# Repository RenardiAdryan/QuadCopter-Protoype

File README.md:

# QuadCopter-Protoype

This project is a basic drone flight controller using PID controller

if you have inquiries
Please feel free to contact me!

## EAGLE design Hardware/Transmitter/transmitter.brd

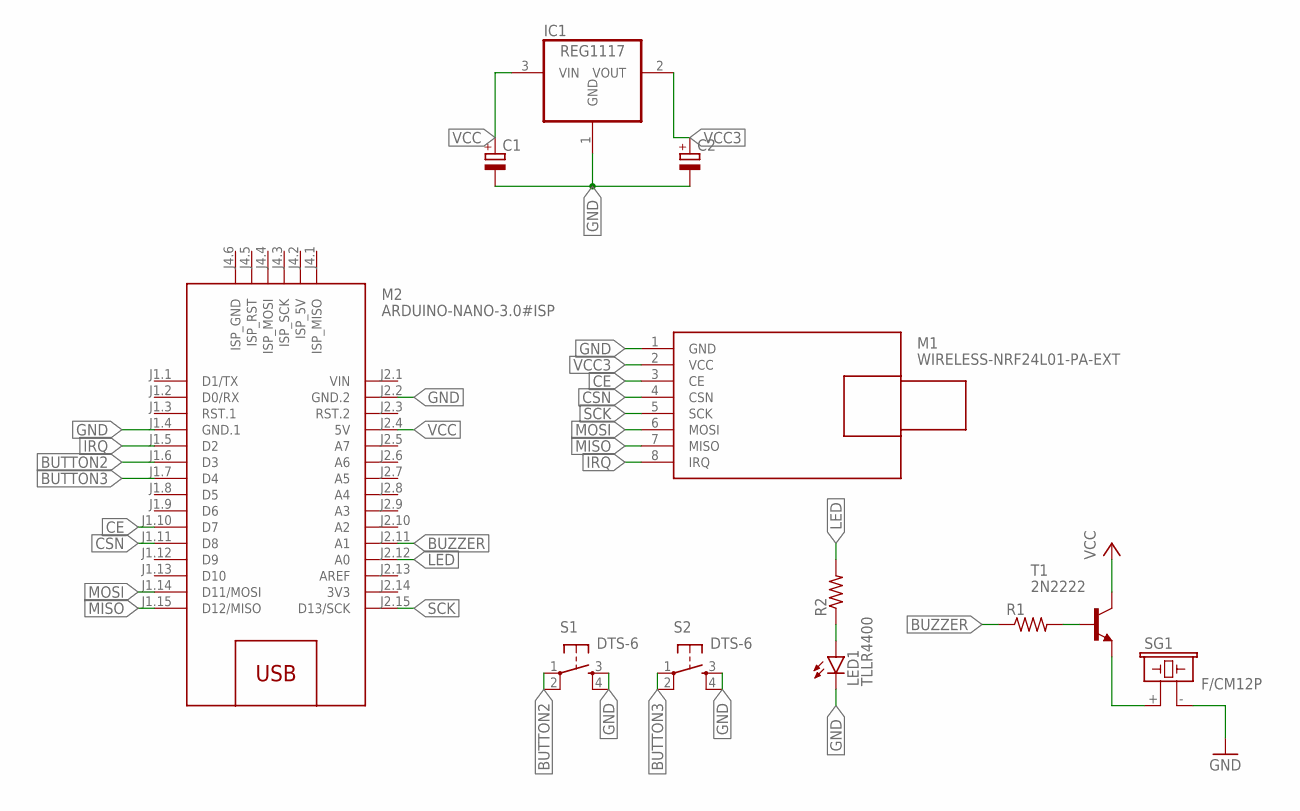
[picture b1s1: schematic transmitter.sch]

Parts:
C1, C2: CPOL-EUE2,5-6E; E2,5-6E
IC1: REG1117; SOT223
LED1: TLLR4400; LED3MM
M1: WIRELESS-NRF24L01-PA-EXT
M2: ARDUINO-NANO-3.0#ISP
R1, R2: R-US_R0805; R0805
S1, S2: DTS-6
SG1: F/CM12P
T1: 2N2222; TO92-EBC-OVAL

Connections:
3V3: M2.J2.14 (3V3)
BUTTON2: M2.J1.6 (D3), S1.1, S1.2
BUTTON3: M2.J1.7 (D4), S2.1, S2.2
BUZZER: M2.J2.11 (A1), R1.1
CE: M1.3 (CE), M2.J1.10 (D7)
CSN: M1.4 (CSN), M2.J1.11 (D8)
GND: C1.-, C2.-, IC1.1 (GND), LED1.K (C), M1.1 (GND), M2.J1.4 (GND.1), M2.J2.2 (GND.2), S1.3, S1.4, S2.3, S2.4, SG1.- (2)
IRQ: M1.8 (IRQ), M2.J1.5 (D2)
LED: M2.J2.12 (A0), R2.2
MISO: M1.7 (MISO), M2.J1.15 (D12/MISO)
MOSI: M1.6 (MOSI), M2.J1.14 (D11/MOSI)
unnamed: SG1.+ (1), T1.E
unnamed: R1.2, T1.B
unnamed: LED1.A, R2.1
SCK: M1.5 (SCK), M2.J2.15 (D13/SCK)
VCC: C1.+, IC1.3 (VIN), M2.J2.4 (5V), T1.C
VCC3: C2.+, IC1.2 (VOUT), M1.2 (VCC)
VIN: M2.J2.1 (VIN)

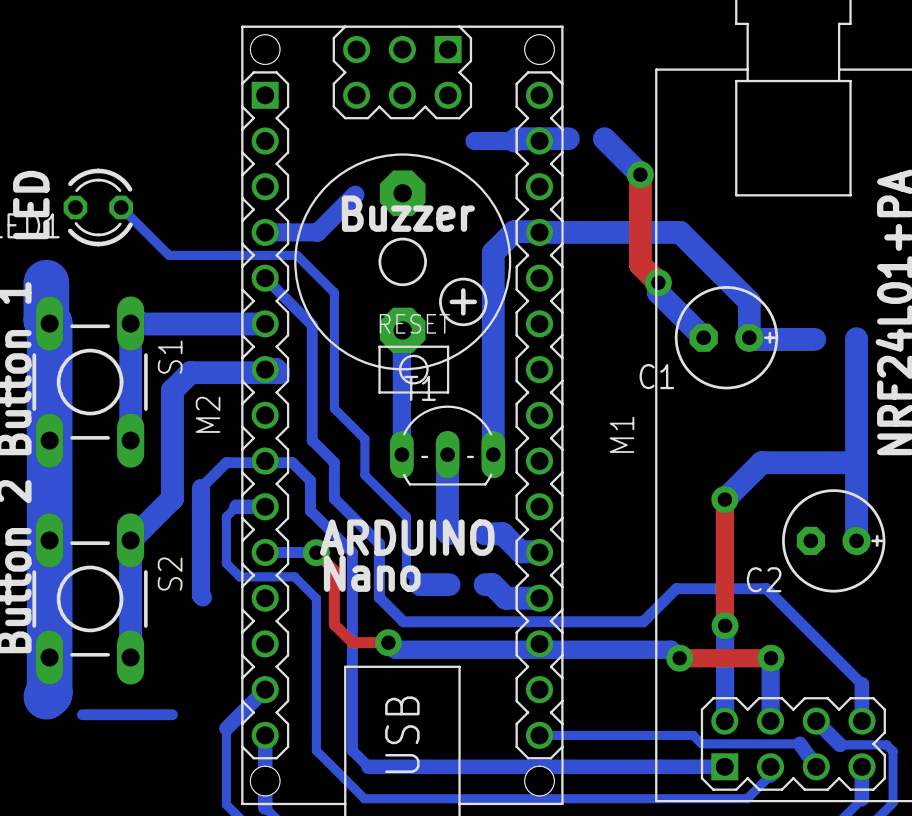
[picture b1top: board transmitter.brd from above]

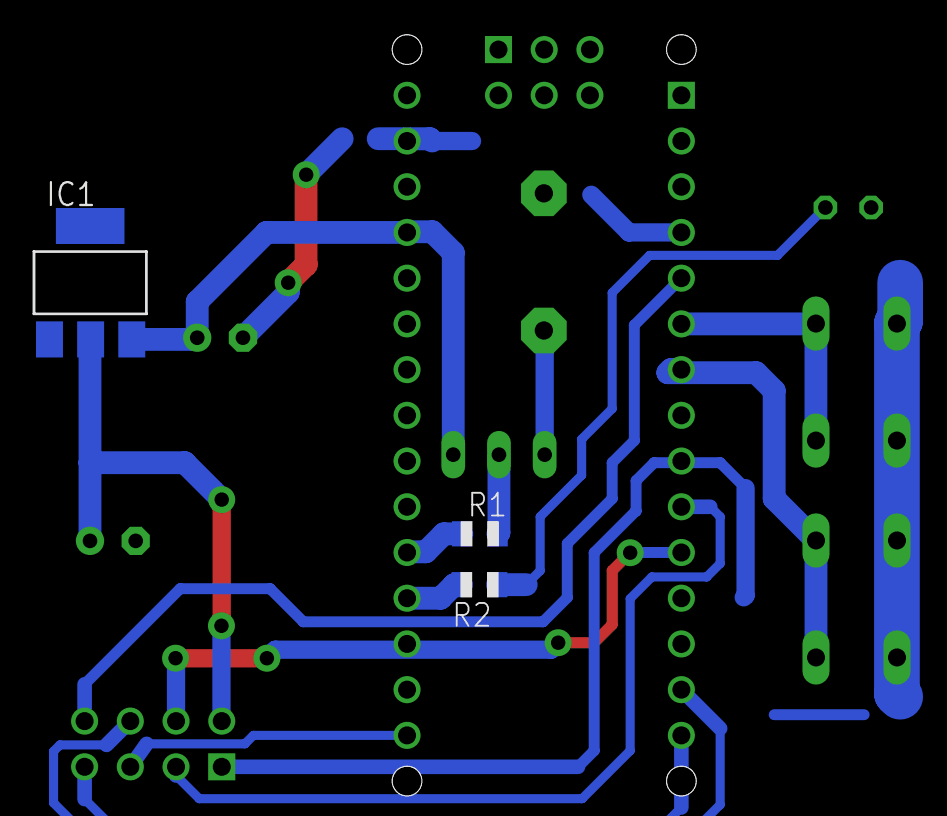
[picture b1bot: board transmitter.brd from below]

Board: 2 copper layers, 12 parts (3 on the bottom side), 16 nets.

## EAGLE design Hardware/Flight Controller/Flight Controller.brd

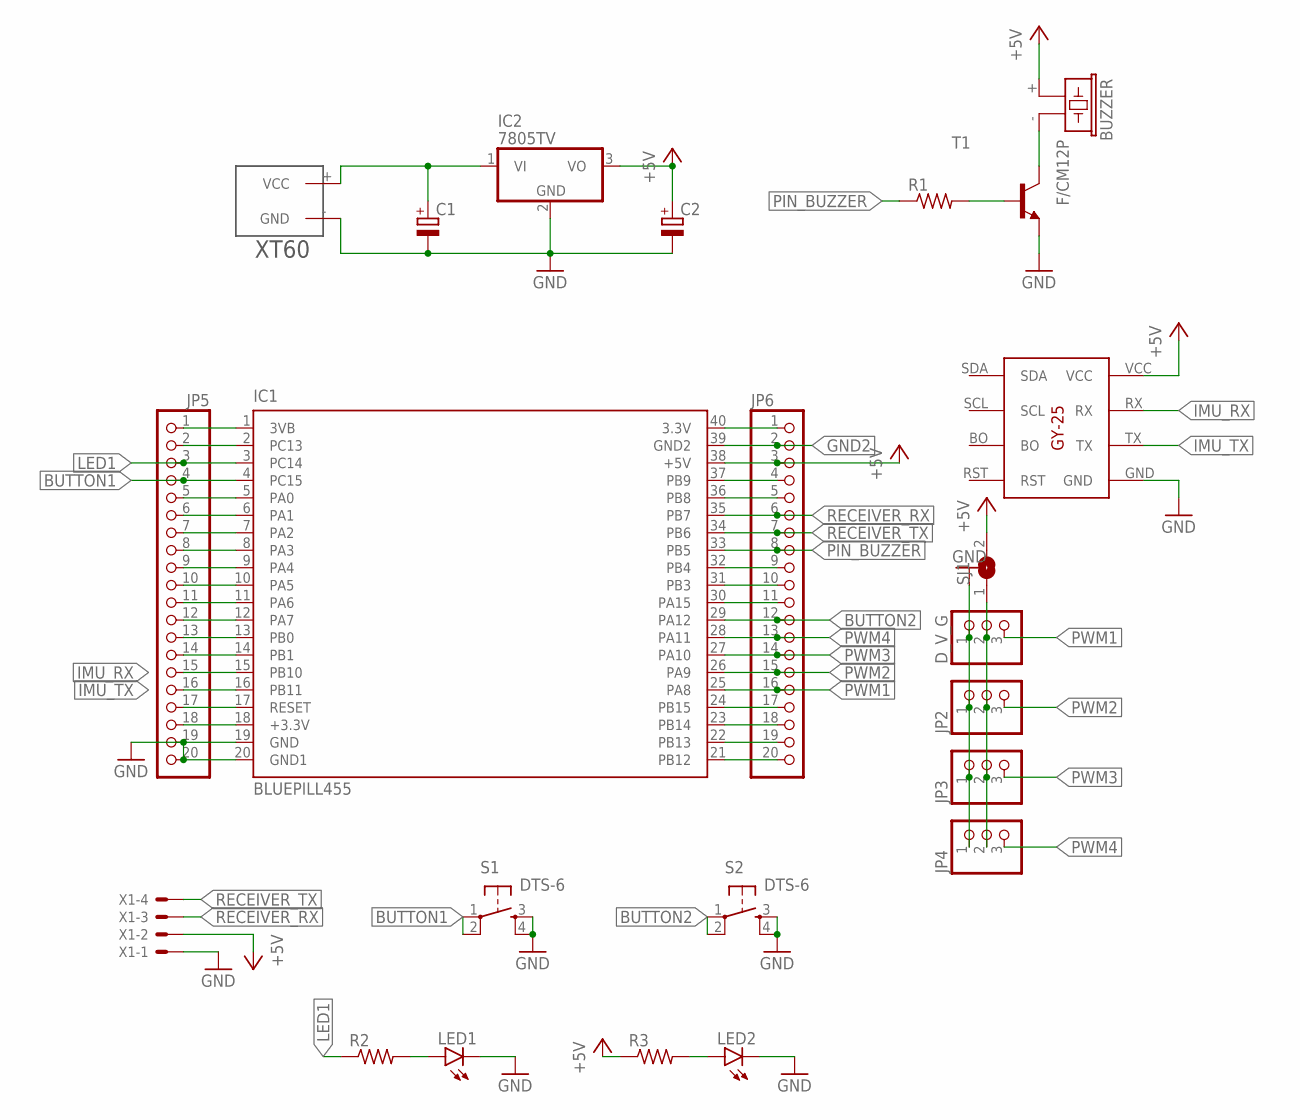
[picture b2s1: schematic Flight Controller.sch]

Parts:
BUZZER: F/CM12P
C1, C2: CPOL-EUE2,5-6E; E2,5-6E
D_V_G: PINHD-1X3; 1X03
GY-1: GY-25GY-25_INV; GY-25_INV
IC1: BLUEPILL455; DIL40
IC2: 7805TV; TO220V
JP2, JP3, JP4: PINHD-1X3; 1X03
JP5, JP6: PINHD-1X20; 1X20
LED1, LED2: LED3MM
R1, R2, R3: R-US_M0805; M0805
S1, S2: DTS-6
SJ1: SJ
T1: -NPN-TO92-EBC; TO92-EBC
U$1: XT60
X1: KK-156-4

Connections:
+5V: BUZZER.+ (1), C2.+, GY-1.VCC, IC1.38 (+5V), IC2.3 (VO), JP6.3, R3.1, SJ1.2, X1.2
BUTTON1: IC1.4 (PC15), JP5.4, S1.1, S1.2
BUTTON2: IC1.29 (PA12), JP6.12, S2.1, S2.2
GND: C1.-, C2.-, D_V_G.1, GY-1.GND, IC1.19 (GND), IC1.20 (GND1), IC2.2 (GND), JP2.1, JP3.1, JP4.1, JP5.19, JP5.20, LED1.K (C), LED2.K (C), S1.3, S1.4, S2.3, S2.4, T1.E, U$1.- (GND), X1.1
GND2: IC1.39 (GND2), JP6.2
IMU_RX: GY-1.RX, IC1.15 (PB10), JP5.15
IMU_TX: GY-1.TX, IC1.16 (PB11), JP5.16
LED1: IC1.3 (PC14), JP5.3, R2.1
unnamed: C1.+, IC2.1 (VI), U$1.+ (VCC)
unnamed: BUZZER.- (2), T1.C
unnamed: IC1.18 (+3.3V), JP5.18
unnamed: R1.2, T1.B
unnamed: IC1.17 (RESET), JP5.17
unnamed: IC1.14 (PB1), JP5.14
unnamed: IC1.13 (PB0), JP5.13
unnamed: IC1.12 (PA7), JP5.12
unnamed: IC1.11 (PA6), JP5.11
unnamed: IC1.10 (PA5), JP5.10
unnamed: IC1.9 (PA4), JP5.9
unnamed: IC1.8 (PA3), JP5.8
unnamed: IC1.7 (PA2), JP5.7
unnamed: IC1.6 (PA1), JP5.6
unnamed: IC1.5 (PA0), JP5.5
unnamed: LED1.A, R2.2
unnamed: LED2.A, R3.2
unnamed: IC1.2 (PC13), JP5.2
unnamed: IC1.1 (3VB), JP5.1
unnamed: IC1.40 (3.3V), JP6.1
unnamed: IC1.37 (PB9), JP6.4
unnamed: IC1.36 (PB8), JP6.5
unnamed: D_V_G.2, JP2.2, JP3.2, JP4.2, SJ1.1
unnamed: IC1.32 (PB4), JP6.9
unnamed: IC1.31 (PB3), JP6.10
unnamed: IC1.30 (PA15), JP6.11
unnamed: IC1.24 (PB15), JP6.17
unnamed: IC1.23 (PB14), JP6.18
unnamed: IC1.22 (PB13), JP6.19
unnamed: IC1.21 (PB12), JP6.20
PIN_BUZZER: IC1.33 (PB5), JP6.8, R1.1
PWM1: D_V_G.3, IC1.25 (PA8), JP6.16
PWM2: IC1.26 (PA9), JP2.3, JP6.15
PWM3: IC1.27 (PA10), JP3.3, JP6.14
PWM4: IC1.28 (PA11), JP4.3, JP6.13
RECEIVER_RX: IC1.35 (PB7), JP6.6, X1.3
RECEIVER_TX: IC1.34 (PB6), JP6.7, X1.4

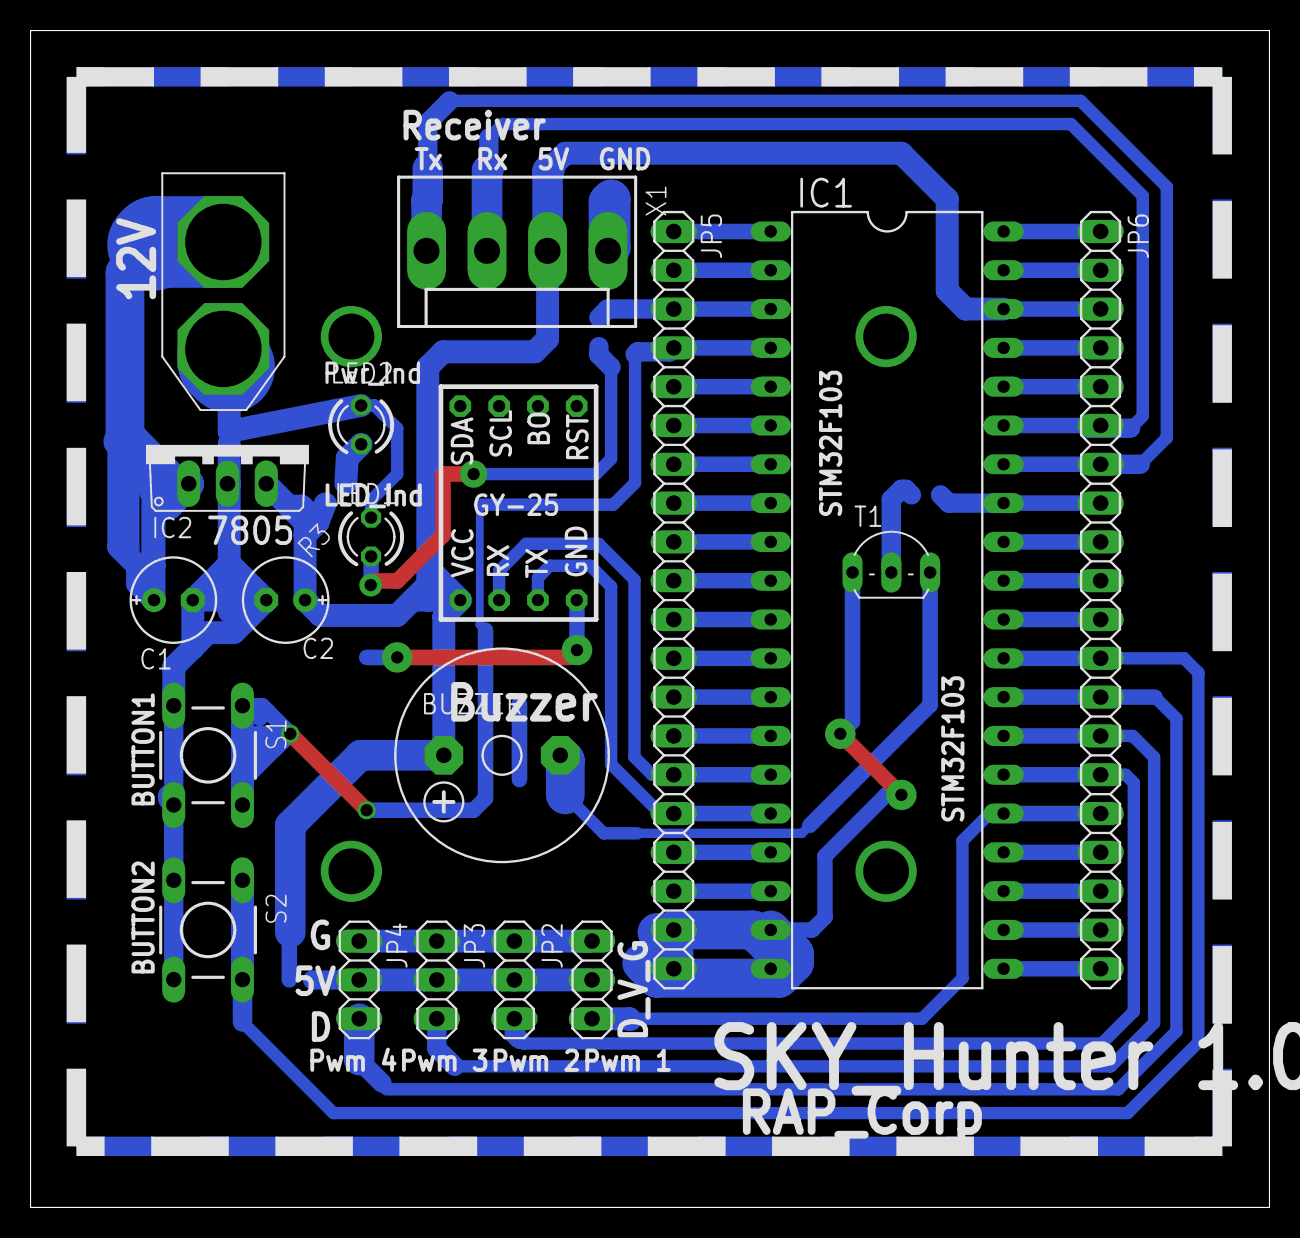
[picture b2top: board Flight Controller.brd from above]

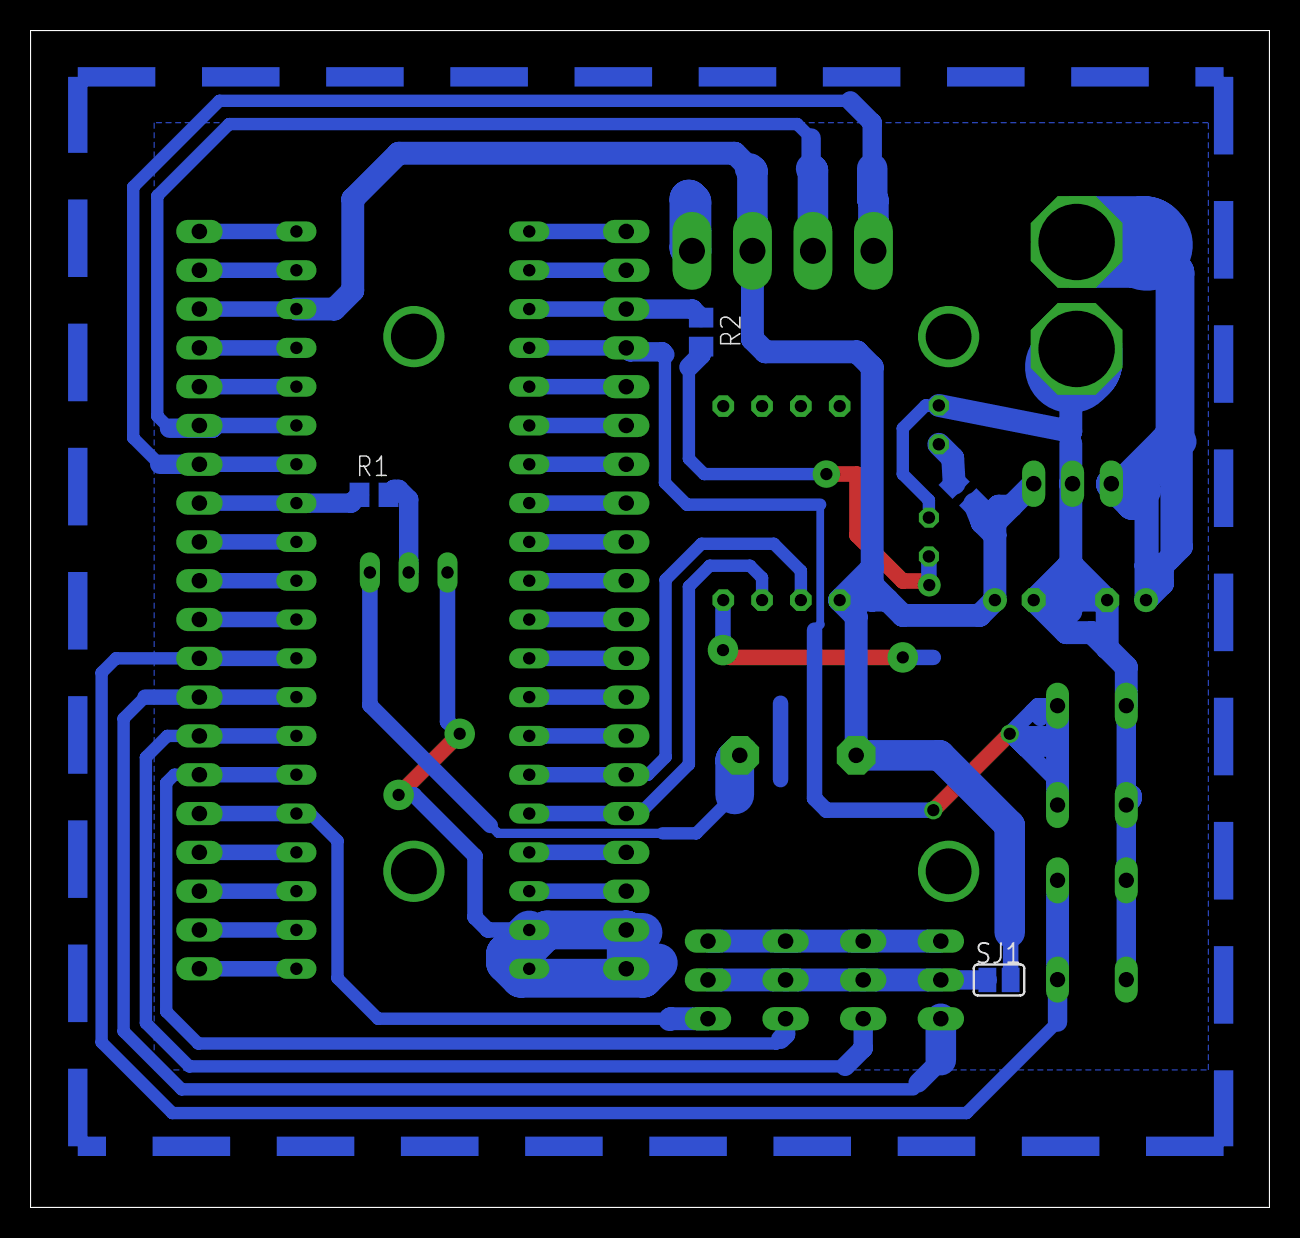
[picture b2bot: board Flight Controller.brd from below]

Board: 2 copper layers, 81.1 x 77.0 mm, 23 parts (4 on the bottom side), 45 nets.

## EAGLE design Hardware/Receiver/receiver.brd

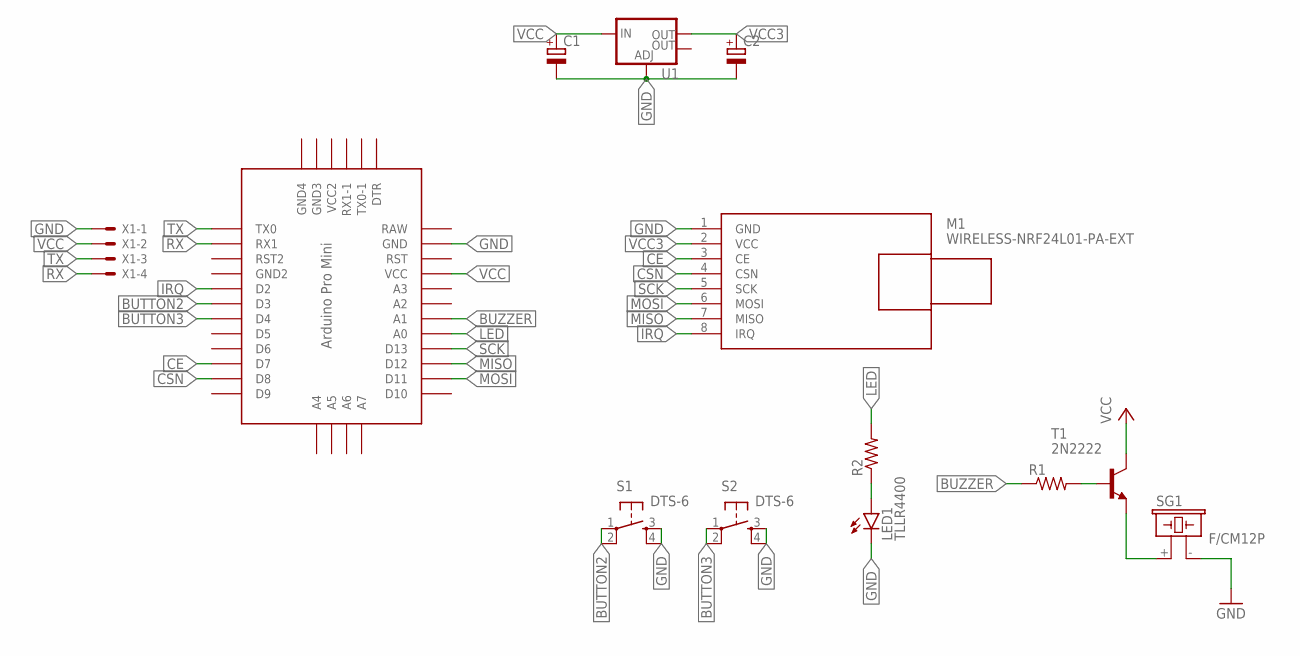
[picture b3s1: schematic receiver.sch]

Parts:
C1, C2: CPOL-EUE2,5-6E; E2,5-6E
LED1: TLLR4400; LED3MM
M1: WIRELESS-NRF24L01-PA-EXT
R1, R2: R-US_R0805; R0805
S1, S2: DTS-6
SG1: F/CM12P
T1: 2N2222; TO92-EBC-OVAL
U1: V_REG_LM1117SOT223; SOT223
U$1: PRO-MINI
X1: KK-156-4

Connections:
BUTTON2: S1.1, S1.2, U$1.D3
BUTTON3: S2.1, S2.2, U$1.D4
BUZZER: R1.1, U$1.A1
CE: M1.3 (CE), U$1.D7
CSN: M1.4 (CSN), U$1.D8
GND: C1.-, C2.-, LED1.K (C), M1.1 (GND), S1.3, S1.4, S2.3, S2.4, SG1.- (2), U1.1 (ADJ), U$1.GND, X1.1
IRQ: M1.8 (IRQ), U$1.D2
LED: R2.2, U$1.A0
MISO: M1.7 (MISO), U$1.D12
MOSI: M1.6 (MOSI), U$1.D11
unnamed: SG1.+ (1), T1.E
unnamed: R1.2, T1.B
unnamed: LED1.A, R2.1
RAW: U$1.RAW
RX: U$1.RX1, X1.4
SCK: M1.5 (SCK), U$1.D13
TX: U$1.TX0, X1.3
VCC: C1.+, T1.C, U1.3 (IN), U$1.VCC, X1.2
VCC3: C2.+, M1.2 (VCC), U1.2 (OUT)

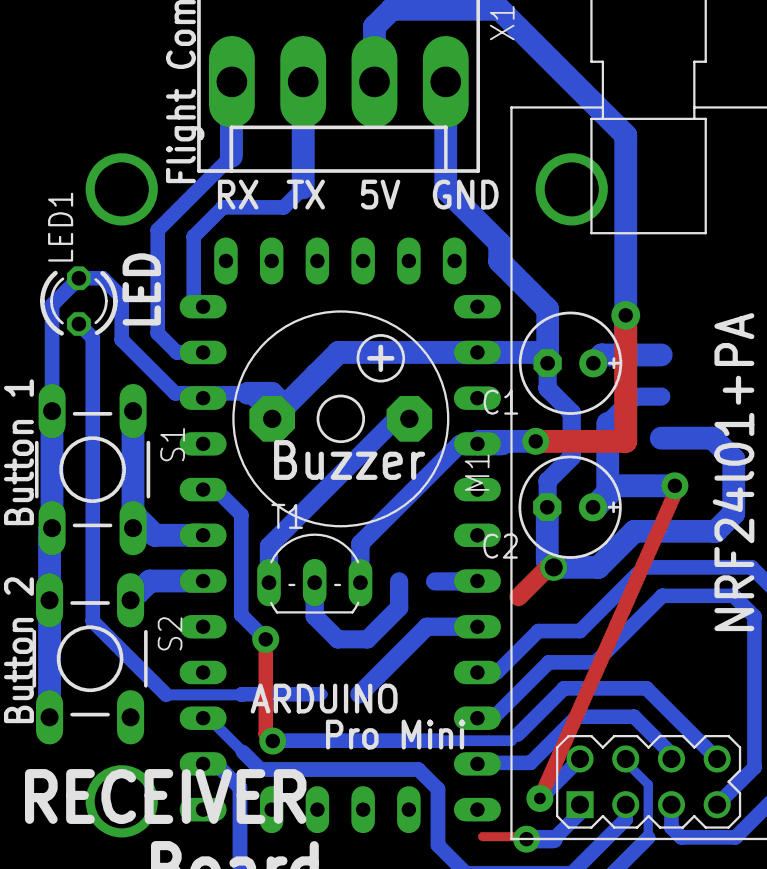
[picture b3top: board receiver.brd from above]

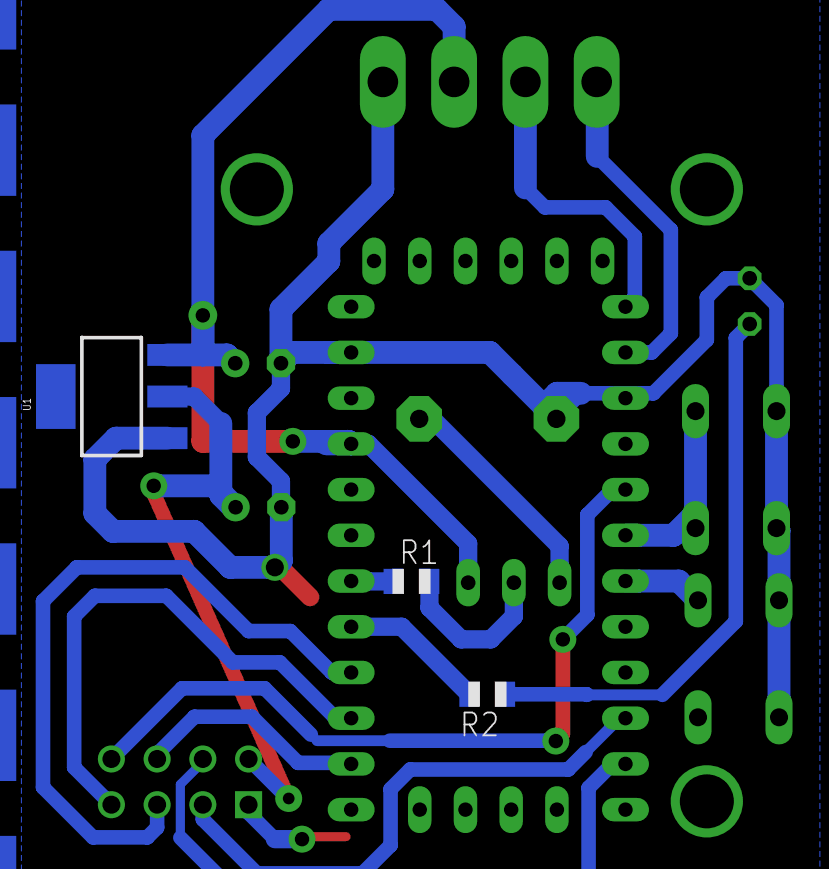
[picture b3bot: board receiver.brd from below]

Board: 2 copper layers, 13 parts (3 on the bottom side), 18 nets.

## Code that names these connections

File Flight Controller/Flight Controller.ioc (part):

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Mcu.Name=STM32F103C(8-B)Tx
Mcu.Package=LQFP48
Mcu.UserName=STM32F103C8Tx
PA10.Signal=S_TIM1_CH3
PA11.Signal=S_TIM1_CH4
PA12.GPIOParameters=GPIO_PuPd
PA12.GPIO_PuPd=GPIO_PULLUP
PA12.Signal=GPIO_Input
PA13.Mode=Serial_Wire
PA13.Signal=SYS_JTMS-SWDIO
PA14.Mode=Serial_Wire
PA14.Signal=SYS_JTCK-SWCLK
PA8.Signal=S_TIM1_CH1
PA9.Signal=S_TIM1_CH2
PB10.Mode=Asynchronous
PB10.Signal=USART3_TX
PB11.Mode=Asynchronous
PB11.Signal=USART3_RX
PB5.Signal=GPIO_Output
PB6.Mode=Asynchronous
PB6.Signal=USART1_TX
PB7.Mode=Asynchronous
PB7.Signal=USART1_RX
PC13-TAMPER-RTC.Signal=GPIO_Output
PC14-OSC32_IN.Signal=GPIO_Output
PC15-OSC32_OUT.GPIOParameters=GPIO_PuPd
PC15-OSC32_OUT.GPIO_PuPd=GPIO_PULLUP
PC15-OSC32_OUT.Signal=GPIO_Input
PD0-OSC_IN.Mode=HSE-External-Oscillator
PD0-OSC_IN.Signal=RCC_OSC_IN
PD1-OSC_OUT.Mode=HSE-External-Oscillator
PD1-OSC_OUT.Signal=RCC_OSC_OUT
RCC.SYSCLKFreq_VALUE=72000000
RCC.SYSCLKSource=RCC_SYSCLKSOURCE_PLLCLK
board=custom

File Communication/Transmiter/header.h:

#ifndef HEADER_H
#define HEADER_H

#include <avr/sleep.h>
#include <nRF24L01.h> //nRF2401 libarary found at https://github.com/tmrh20/RF24/
#include <RF24.h> //nRF2401 libarary found at https://github.com/tmrh20/RF24/



#define BAUDRATE 9600
#define PUSHBUTTON1 3
#define PUSHBUTTON2 4
#define IRQ 2

#define LED1 A0
#define BUZZER A1

#define CSN  8
#define CE   7


#endif

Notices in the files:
parts and their libraries:
Diy Library: Released under the Creative Commons Attribution 4.0 International License: http://creativecommons.org/licenses/by/4.0
SparkFun-IC-Power: Licensing: Creative Commons ShareAlike 4.0 International - https://creativecommons.org/licenses/by-sa/4.0
